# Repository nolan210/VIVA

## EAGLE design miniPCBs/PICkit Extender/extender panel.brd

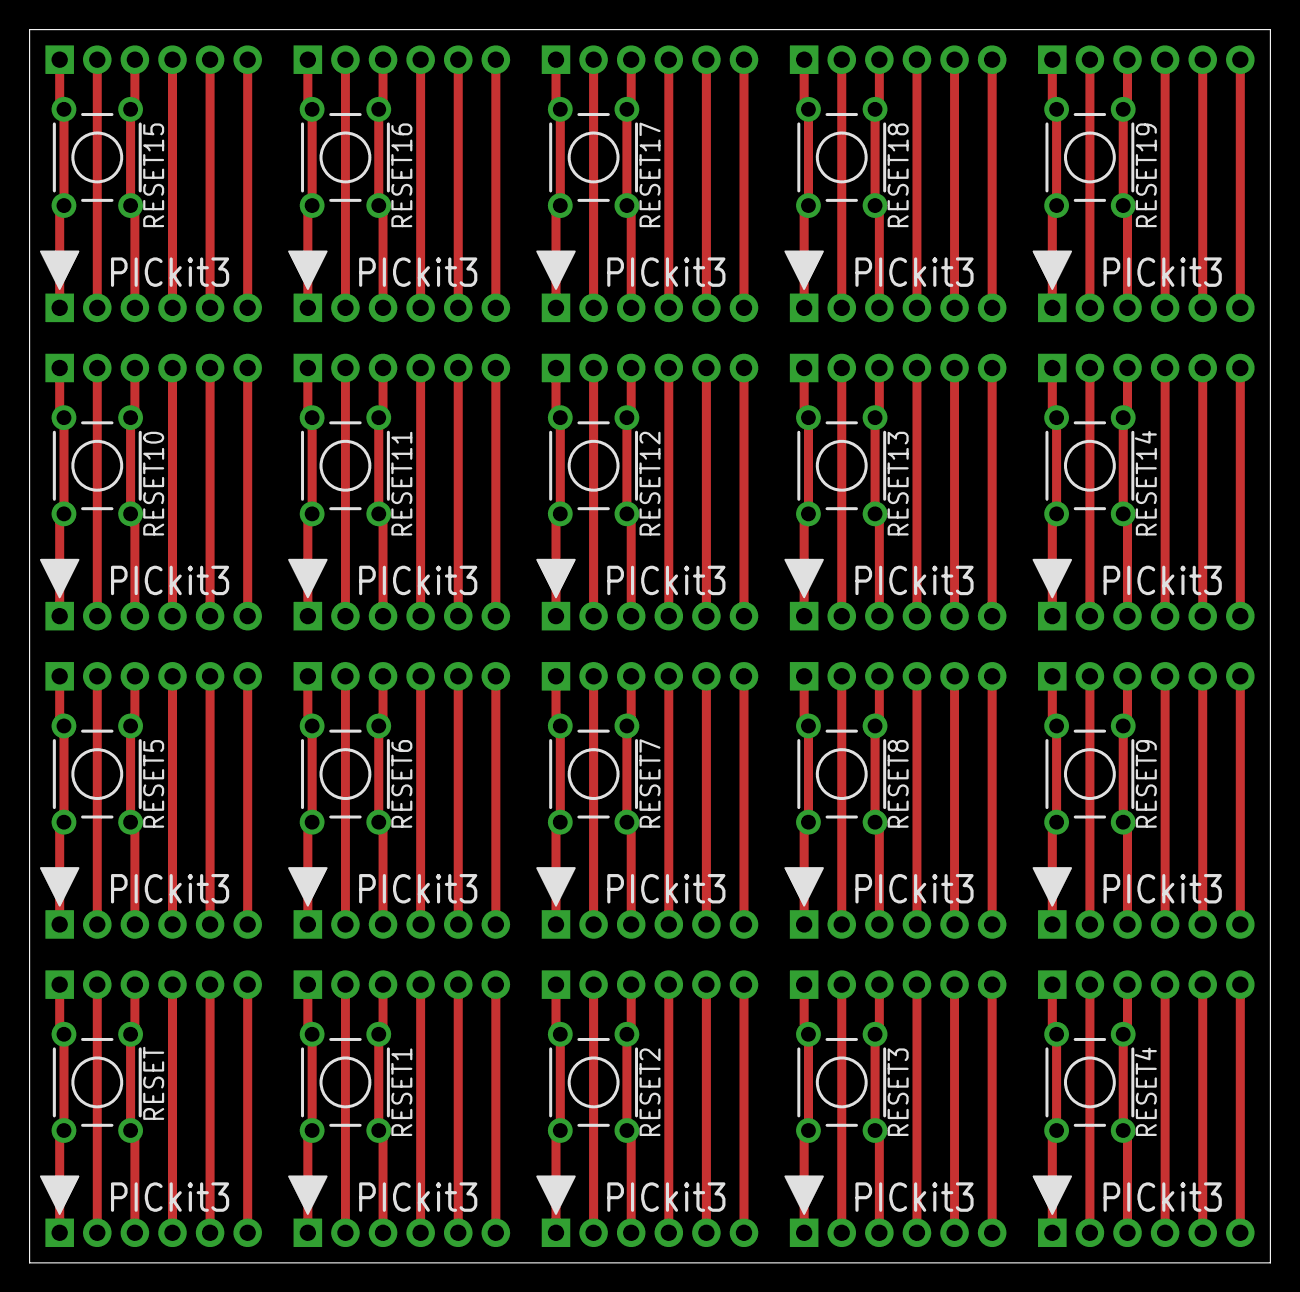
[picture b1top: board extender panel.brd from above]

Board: 2 copper layers, 83.8 x 83.3 mm, 60 parts (0 on the bottom side), 120 nets.

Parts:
RESET, RESET1, RESET2, RESET3, RESET4, RESET5, RESET6, RESET7, RESET8, RESET9, RESET10, RESET11, RESET12, RESET13, RESET14, RESET15, RESET16, RESET17, RESET18, RESET19: TL1105
U$1, U$2, U$5, U$7, U$9, U$11, U$13, U$15, U$17, U$19, U$21, U$23, U$25, U$27, U$29, U$31, U$33, U$35, U$37, U$39: PICKIT3; PINS_6_PICKIT3
U$3, U$4, U$6, U$8, U$10, U$12, U$14, U$16, U$18, U$20, U$22, U$24, U$26, U$28, U$30, U$32, U$34, U$36, U$38, U$40: PICKIT3PLAIN; PINS_6

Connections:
unnamed: RESET.2, RESET.4, U$1.1, U$3.1
unnamed: U$1.2, U$3.2
unnamed: RESET.1, RESET.3, U$1.3, U$3.3
unnamed: U$1.4, U$3.4
unnamed: U$1.5, U$3.5
unnamed: U$1.6, U$3.6
unnamed: RESET1.2, RESET1.4, U$2.1, U$4.1
unnamed: U$2.2, U$4.2
unnamed: RESET1.1, RESET1.3, U$2.3, U$4.3
unnamed: U$2.4, U$4.4
unnamed: U$2.5, U$4.5
unnamed: U$2.6, U$4.6
unnamed: RESET2.2, RESET2.4, U$5.1, U$6.1
unnamed: U$5.2, U$6.2
unnamed: RESET2.1, RESET2.3, U$5.3, U$6.3
unnamed: U$5.4, U$6.4
unnamed: U$5.5, U$6.5
unnamed: U$5.6, U$6.6
unnamed: RESET3.2, RESET3.4, U$7.1, U$8.1
unnamed: U$7.2, U$8.2
unnamed: RESET3.1, RESET3.3, U$7.3, U$8.3
unnamed: U$7.4, U$8.4
unnamed: U$7.5, U$8.5
unnamed: U$7.6, U$8.6
unnamed: RESET4.2, RESET4.4, U$9.1, U$10.1
unnamed: U$9.2, U$10.2
unnamed: RESET4.1, RESET4.3, U$9.3, U$10.3
unnamed: U$9.4, U$10.4
unnamed: U$9.5, U$10.5
unnamed: U$9.6, U$10.6
unnamed: RESET5.2, RESET5.4, U$11.1, U$12.1
unnamed: U$11.2, U$12.2
unnamed: RESET5.1, RESET5.3, U$11.3, U$12.3
unnamed: U$11.4, U$12.4
unnamed: U$11.5, U$12.5
unnamed: U$11.6, U$12.6
unnamed: RESET6.2, RESET6.4, U$13.1, U$14.1
unnamed: U$13.2, U$14.2
unnamed: RESET6.1, RESET6.3, U$13.3, U$14.3
unnamed: U$13.4, U$14.4
unnamed: U$13.5, U$14.5
unnamed: U$13.6, U$14.6
unnamed: RESET7.2, RESET7.4, U$15.1, U$16.1
unnamed: U$15.2, U$16.2
unnamed: RESET7.1, RESET7.3, U$15.3, U$16.3
unnamed: U$15.4, U$16.4
unnamed: U$15.5, U$16.5
unnamed: U$15.6, U$16.6
unnamed: RESET8.2, RESET8.4, U$17.1, U$18.1
unnamed: U$17.2, U$18.2
unnamed: RESET8.1, RESET8.3, U$17.3, U$18.3
unnamed: U$17.4, U$18.4
unnamed: U$17.5, U$18.5
unnamed: U$17.6, U$18.6
unnamed: RESET9.2, RESET9.4, U$19.1, U$20.1
unnamed: U$19.2, U$20.2
unnamed: RESET9.1, RESET9.3, U$19.3, U$20.3
unnamed: U$19.4, U$20.4
unnamed: U$19.5, U$20.5
unnamed: U$19.6, U$20.6
unnamed: RESET10.2, RESET10.4, U$21.1, U$22.1
unnamed: U$21.2, U$22.2
unnamed: RESET10.1, RESET10.3, U$21.3, U$22.3
unnamed: U$21.4, U$22.4
unnamed: U$21.5, U$22.5
unnamed: U$21.6, U$22.6
unnamed: RESET11.2, RESET11.4, U$23.1, U$24.1
unnamed: U$23.2, U$24.2
unnamed: RESET11.1, RESET11.3, U$23.3, U$24.3
unnamed: U$23.4, U$24.4
unnamed: U$23.5, U$24.5
unnamed: U$23.6, U$24.6
unnamed: RESET12.2, RESET12.4, U$25.1, U$26.1
unnamed: U$25.2, U$26.2
unnamed: RESET12.1, RESET12.3, U$25.3, U$26.3
unnamed: U$25.4, U$26.4
unnamed: U$25.5, U$26.5
unnamed: U$25.6, U$26.6
unnamed: RESET13.2, RESET13.4, U$27.1, U$28.1
unnamed: U$27.2, U$28.2
unnamed: RESET13.1, RESET13.3, U$27.3, U$28.3
unnamed: U$27.4, U$28.4
unnamed: U$27.5, U$28.5
unnamed: U$27.6, U$28.6
unnamed: RESET14.2, RESET14.4, U$29.1, U$30.1
unnamed: U$29.2, U$30.2
unnamed: RESET14.1, RESET14.3, U$29.3, U$30.3
unnamed: U$29.4, U$30.4
unnamed: U$29.5, U$30.5
unnamed: U$29.6, U$30.6
unnamed: RESET15.2, RESET15.4, U$31.1, U$32.1
unnamed: U$31.2, U$32.2
unnamed: RESET15.1, RESET15.3, U$31.3, U$32.3
unnamed: U$31.4, U$32.4
unnamed: U$31.5, U$32.5
unnamed: U$31.6, U$32.6
unnamed: RESET16.2, RESET16.4, U$33.1, U$34.1
unnamed: U$33.2, U$34.2
unnamed: RESET16.1, RESET16.3, U$33.3, U$34.3
unnamed: U$33.4, U$34.4
unnamed: U$33.5, U$34.5
unnamed: U$33.6, U$34.6
unnamed: RESET17.2, RESET17.4, U$35.1, U$36.1
unnamed: U$35.2, U$36.2
unnamed: RESET17.1, RESET17.3, U$35.3, U$36.3
unnamed: U$35.4, U$36.4
unnamed: U$35.5, U$36.5
unnamed: U$35.6, U$36.6
unnamed: RESET18.2, RESET18.4, U$37.1, U$38.1
unnamed: U$37.2, U$38.2
unnamed: RESET18.1, RESET18.3, U$37.3, U$38.3
unnamed: U$37.4, U$38.4
unnamed: U$37.5, U$38.5
unnamed: U$37.6, U$38.6
unnamed: RESET19.2, RESET19.4, U$39.1, U$40.1
unnamed: U$39.2, U$40.2
unnamed: RESET19.1, RESET19.3, U$39.3, U$40.3
unnamed: U$39.4, U$40.4
unnamed: U$39.5, U$40.5
unnamed: U$39.6, U$40.6
